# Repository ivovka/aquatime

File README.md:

# aquatime
Это суточный таймер. На одну нагрузку. Управляется одной кнопкой. Индикация с использованием двух светодиодов.
## Режимы работы
Режимы переключаются длительным нажатием кнопки. Светодиод LED1 индицирует режим, светодиод LED2 в ручном режиме индицирует состояние нагрузки; в автоматическом режиме, кроме состояния нагрузки, индицирует состояние таймера.
### Ручной
Индикатором ручного режима является постоянно горящий светодиод LED1.
В ручном режиме с помощью короткого нажатия кнопки инвертируется состояние нагрузки. Переход в автоматический режим - длинным нажатием кнопки.
### Автоматический
Индикатором автоматического режима является мигание светодиода LED1 с частотой 1Гц.
По короткому нажатию кнопки:
* в состоянии "нагрузка включена" - нагрузка выключается и время выключения нагрузки устанавливается в текущее время;
* в состоянии "нагрузка выключена" - нагрузка включается и таймер сбрасывается, т.е. время включения нагрузки устанавливается в текущее время, время выключения нагрузки - неопределено. Таким образом, нагрузка остается включенной до следующего короткого нажатия кнопки, которое устанавливает время выключения нагрузки.

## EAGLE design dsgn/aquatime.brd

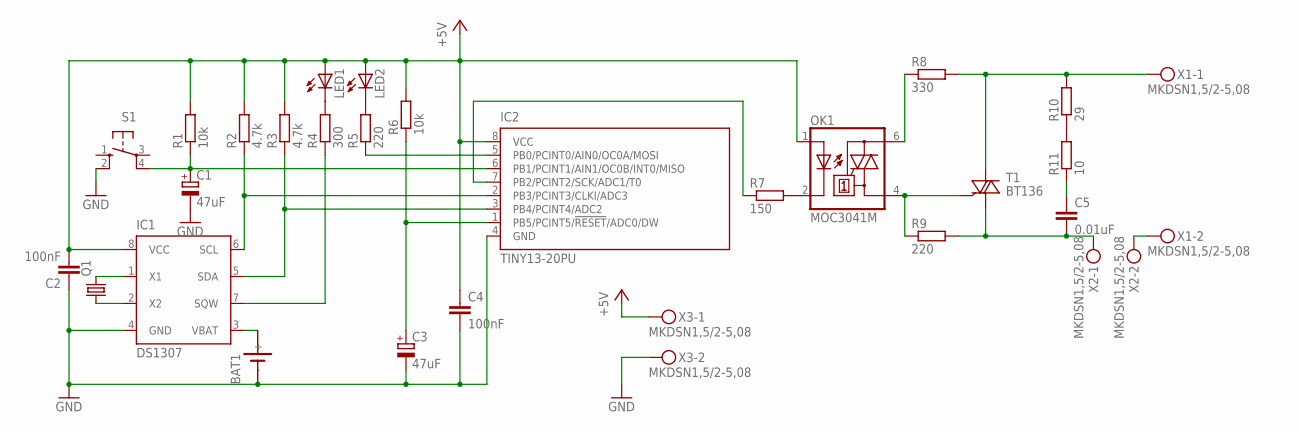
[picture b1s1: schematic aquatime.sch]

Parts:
BAT1: SN2032
C1, C3: 47uF; E2,5-6
C2, C4: 100nF; C102-064X133
C5: 0.01uF; C102-064X133
IC1: DS1307; DIL08
IC2: TINY13-20PU; DIL08
LED1, LED2: LED5MM
OK1: MOC3041M; DIL06
Q1: CRYSTALTC26H; TC26H
R1, R6: 10k; 0207/12
R2, R3: 4.7k; 0207/10
R4: 300; 0207/10
R5: 220; 0207/10
R7: 150; 0207/10
R8: 330; P0817/22
R9: 220; 0411/15
R10: 29; 0411/15
R11: 10; 0411/15
S1: 10-XX; B3F-10XX
T1: BT136; TO220AB
X1, X2, X3: MKDSN1,5/2-5,08

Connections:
+5V: C2.2, C4.1, IC1.8 (VCC), IC2.8 (VCC), LED1.A, LED2.A, OK1.1 (A), R1.2, R2.2, R3.2, R6.2, X3.1
GND: BAT1.-, C1.-, C2.1, C3.-, C4.2, IC1.4 (GND), IC2.4 (GND), S1.2 (S1), X3.2
unnamed: C3.+, IC2.1 (PB5/PCINT5/!RESET!/ADC0/DW), R6.1
unnamed: LED2.K (C), R5.2
unnamed: R10.1, R11.2
unnamed: OK1.2 (C), R7.2
unnamed: BAT1.+, IC1.3 (VBAT)
unnamed: IC2.7 (PB2/PCINT2/SCK/ADC1/T0), R7.1
unnamed: IC1.5 (SDA), IC2.3 (PB4/PCINT4/ADC2), R3.1
unnamed: IC1.6 (SCL), IC2.2 (PB3/PCINT3/CLKI/ADC3), R2.1
unnamed: LED1.K (C), R4.2
unnamed: IC1.7 (SQW), R4.1
unnamed: OK1.6 (A2), R8.1
unnamed: IC1.1 (X1), Q1.2
unnamed: IC1.2 (X2), Q1.1
unnamed: IC2.5 (PB0/PCINT0/AIN0/OC0A/MOSI), R5.1
unnamed: R8.2, R10.2, T1.2 (A2), X1.1
unnamed: OK1.4 (A1), R9.1, T1.3 (G)
unnamed: C5.2, R9.2, T1.1 (A1), X2.1
unnamed: C5.1, R11.1
unnamed: X1.2, X2.2
unnamed: C1.+, IC2.6 (PB1/PCINT1/AIN1/OC0B/INT0/MISO), R1.1, S1.4 (P1)

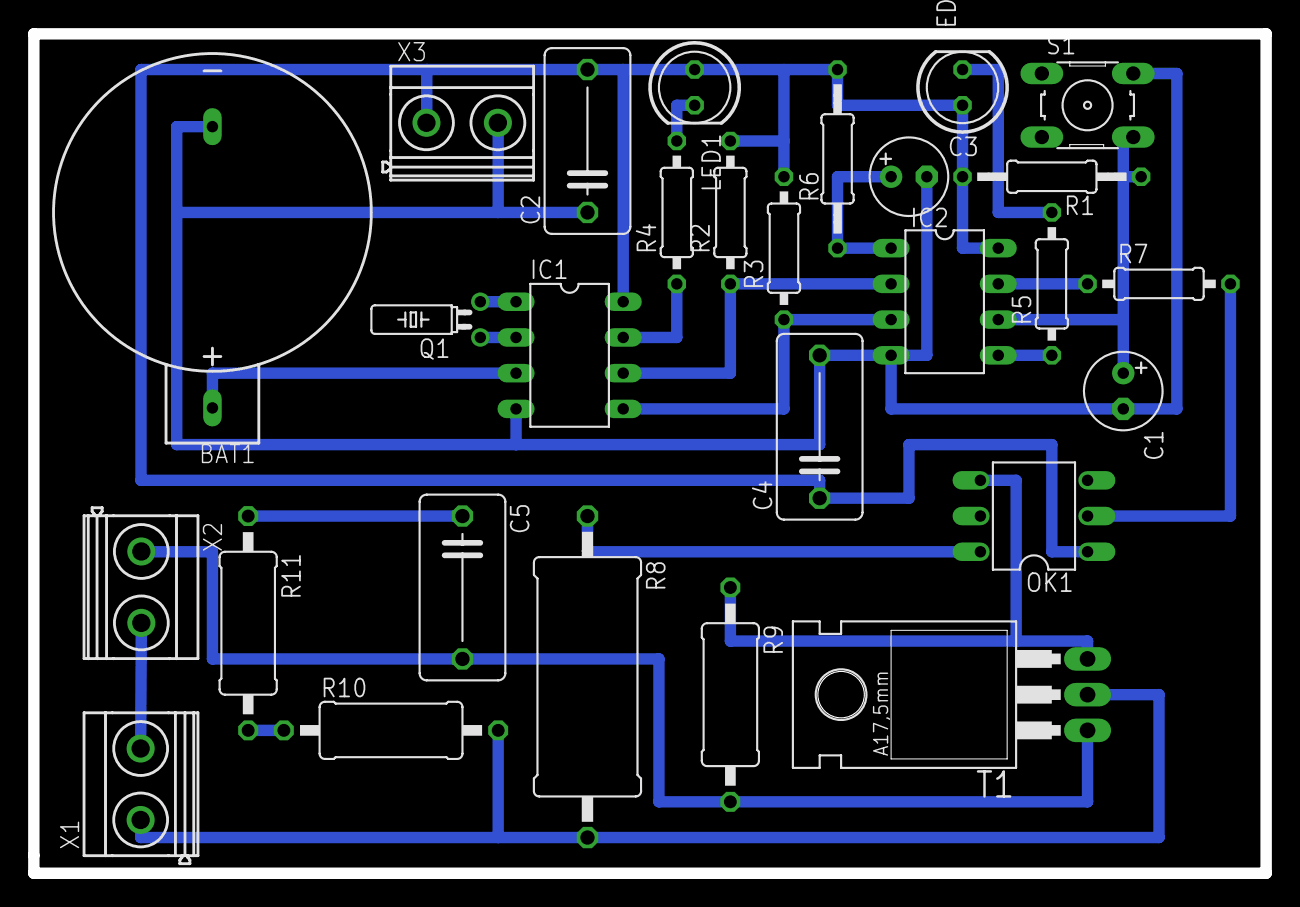
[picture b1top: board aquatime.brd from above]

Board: 2 copper layers, 87.6 x 59.7 mm, 28 parts (0 on the bottom side), 22 nets.
